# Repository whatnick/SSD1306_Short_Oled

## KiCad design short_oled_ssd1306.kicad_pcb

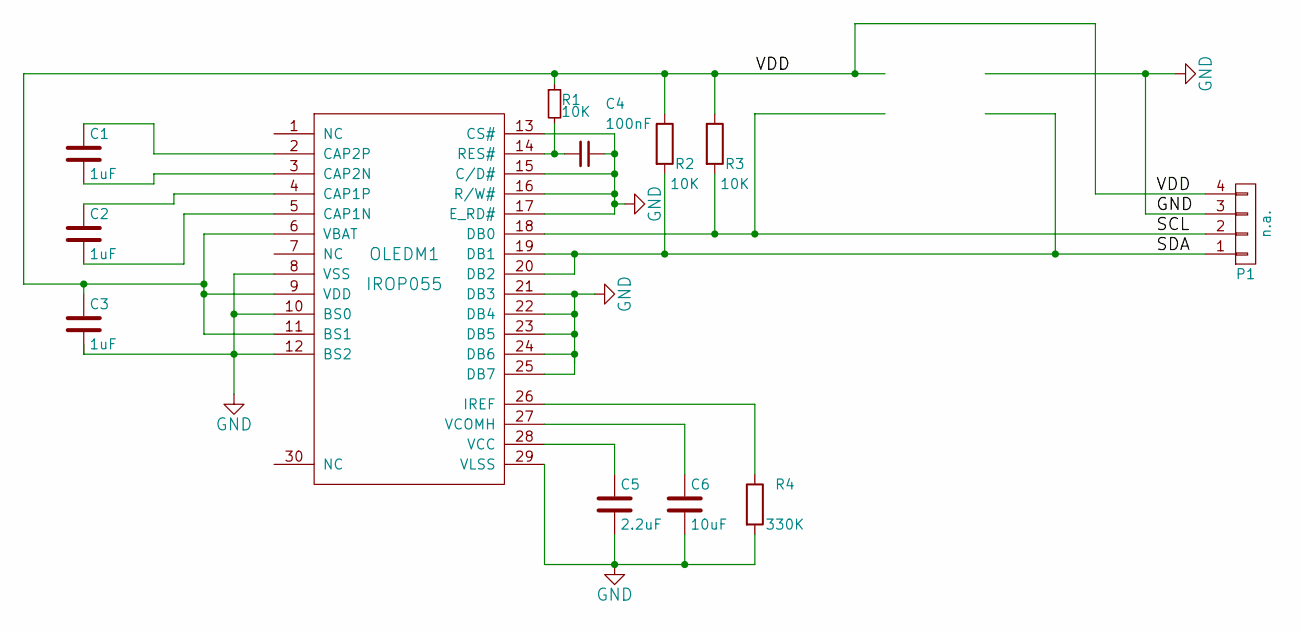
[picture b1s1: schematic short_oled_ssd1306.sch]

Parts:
C1, C2, C3: 1uF; C_0603
C4: 100nF; C_0603
C5: 2.2uF; C_0603
C6: 10uF; C_0603
OLEDM1: IROP055; IROP055-SSD1306Z-PADS-ONLY
P1: n.a.; Socket_Strip_Straight_1x04_Pitch2.54mm
R1, R2, R3: 10K; R_0603
R4: 330K; R_0603

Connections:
/SCL: OLEDM1.18 (DB0), P1.2, R3.2
/SDA: OLEDM1.19 (DB1), OLEDM1.20 (DB2), P1.1, R2.2
/VDD: C3.1, OLEDM1.6 (VBAT), OLEDM1.9 (VDD), OLEDM1.11 (BS1), P1.4, R1.1, R2.1, R3.1
GND: C3.2, C4.1, C5.2, C6.2, OLEDM1.8 (VSS), OLEDM1.10 (BS0), OLEDM1.12 (BS2), OLEDM1.13 (CS#), OLEDM1.15 (C/D#), OLEDM1.16 (R/W#), OLEDM1.17 (E_RD#), OLEDM1.21 (DB3), OLEDM1.22 (DB4), OLEDM1.23 (DB5), OLEDM1.24 (DB6), OLEDM1.25 (DB7), OLEDM1.29 (VLSS), P1.3, R4.2
unnamed: C1.1, OLEDM1.2 (CAP2P)
unnamed: C1.2, OLEDM1.3 (CAP2N)
unnamed: C2.1, OLEDM1.4 (CAP1P)
unnamed: C2.2, OLEDM1.5 (CAP1N)
unnamed: C4.2, OLEDM1.14 (RES#), R1.2
unnamed: C5.1, OLEDM1.28 (VCC)
unnamed: C6.1, OLEDM1.27 (VCOMH)
unnamed: OLEDM1.26 (IREF), R4.1

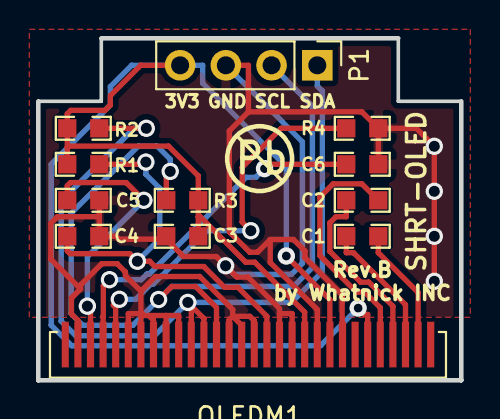
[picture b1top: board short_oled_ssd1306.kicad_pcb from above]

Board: 2 copper layers, 23.5 x 19.0 mm, 12 parts (0 on the bottom side), 12 nets.

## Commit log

2018-09-13 Initial import
2018-10-17 Add tags to pins
